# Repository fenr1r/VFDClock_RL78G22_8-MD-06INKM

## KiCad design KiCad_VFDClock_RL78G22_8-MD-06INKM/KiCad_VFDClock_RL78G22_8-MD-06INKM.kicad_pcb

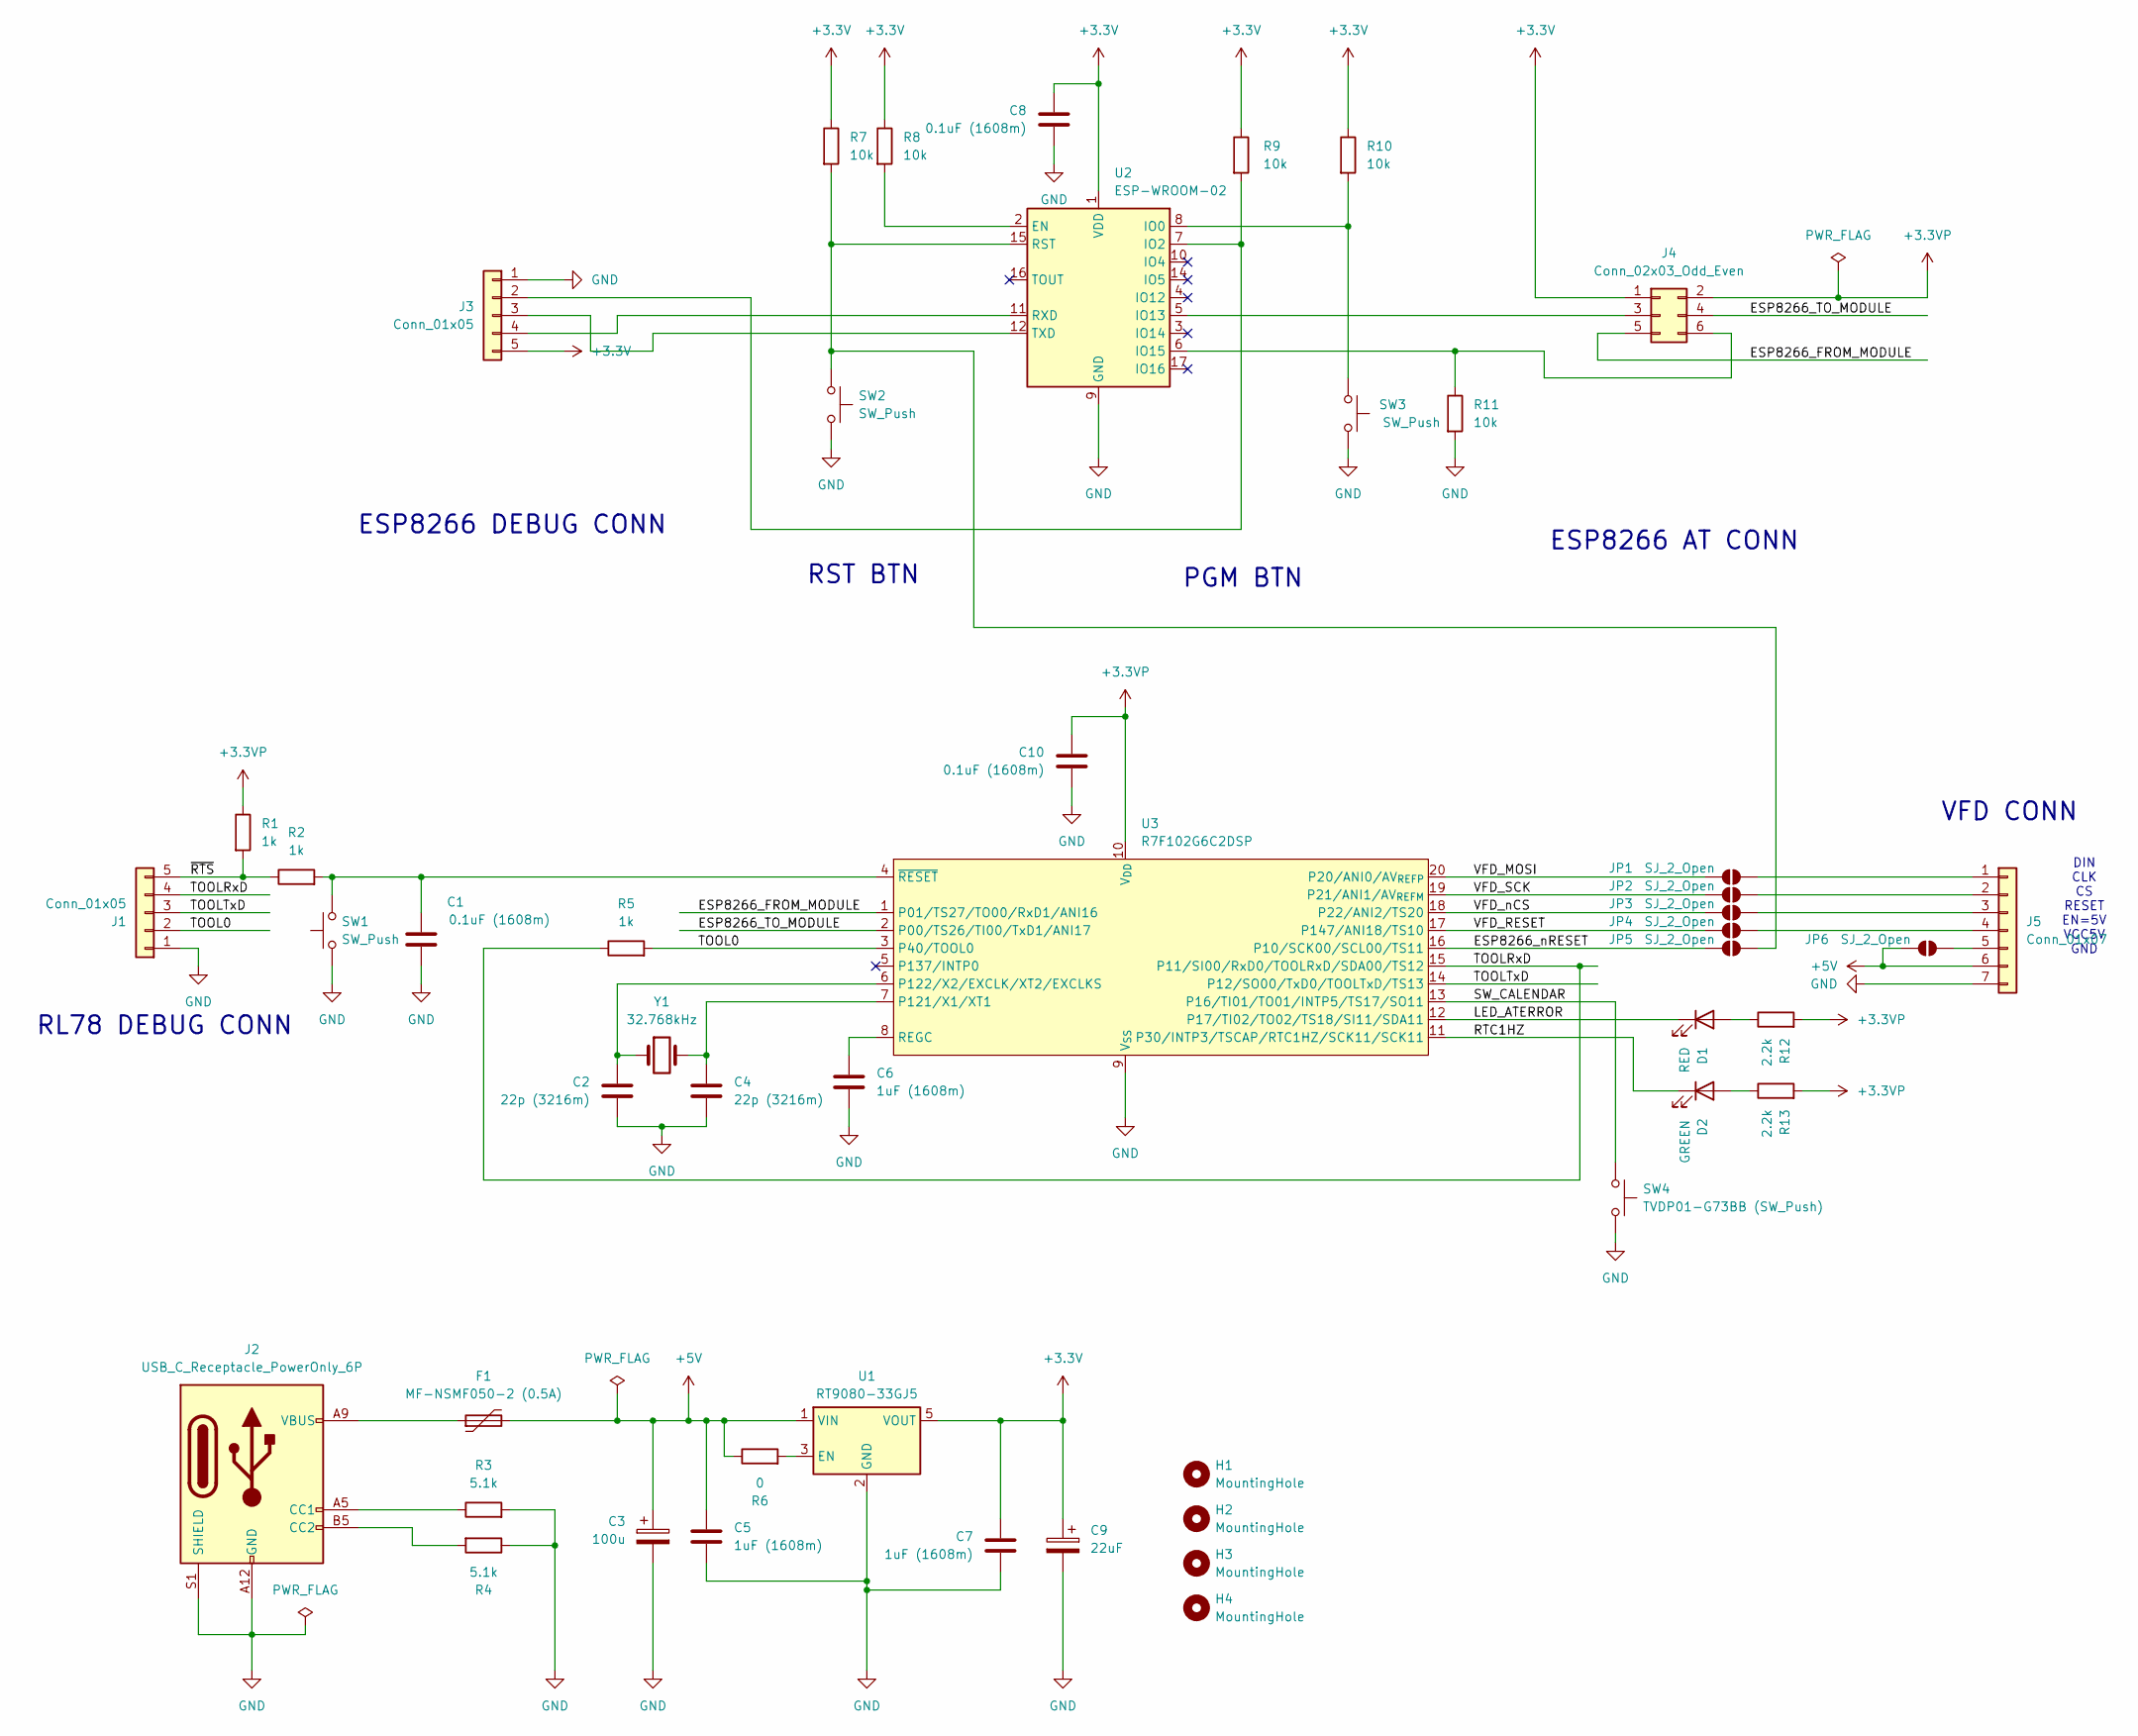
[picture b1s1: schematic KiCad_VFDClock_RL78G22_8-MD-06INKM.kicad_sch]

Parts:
C1, C8, C10: 0.1uF (1608m); C_0603_1608Metric_Pad1.08x0.95mm_HandSolder
C2, C4: 22p (3216m); C_1206_3216Metric_Pad1.33x1.80mm_HandSolder
C3: 100u; CP_Radial_D6.3mm_P2.50mm
C5, C6, C7: 1uF (1608m); C_0603_1608Metric_Pad1.08x0.95mm_HandSolder
C9: 22uF; CP_Radial_Tantal_D4.5mm_P2.50mm
D1: RED; LED_0603_1608Metric_Pad1.05x0.95mm_HandSolder
D2: GREEN; LED_0603_1608Metric_Pad1.05x0.95mm_HandSolder
F1: MF-NSMF050-2 (0.5A); C_1812_4532Metric_Pad1.57x3.40mm_HandSolder
H1, H2, H3, H4: MountingHole; MountingHole_2.2mm_M2
J1, J3: Conn_01x05; ConThrough_XB-3_1x05_P2.54mm_Vertical
J2: USB_C_Receptacle_PowerOnly_6P; USB_C_Receptacle_GCT_USB4125-xx-x_6P_TopMnt_Horizontal
J4: Conn_02x03_Odd_Even; PinHeader_2x03_P2.54mm_Vertical_SMD
J5: Conn_01x07; PinHeader_1x07_P2.54mm_Vertical
JP1, JP2, JP3, JP4, JP5, JP6: SJ_2_Open; SolderJumper-2_P1.3mm_Open_RoundedPad1.0x1.5mm
R1, R2, R5: 1k; R_0603_1608Metric_Pad0.98x0.95mm_HandSolder
R3, R4: 5.1k; R_0603_1608Metric_Pad0.98x0.95mm_HandSolder
R6: 0; R_0603_1608Metric_Pad0.98x0.95mm_HandSolder
R7, R8, R9, R10, R11: 10k; R_0603_1608Metric_Pad0.98x0.95mm_HandSolder
R12, R13: 2.2k; R_0603_1608Metric_Pad0.98x0.95mm_HandSolder
SW1, SW2, SW3: SW_Push; SW_PUSH_1P1T_6x3.5mm_H4.3_APEM_MJTP1243
SW4: TVDP01-G73BB (SW_Push); SW_PUSH_6mm
U1: RT9080-33GJ5; TSOT-23-5_HandSoldering
U2: ESP-WROOM-02
U3: R7F102G6C2DSP; TSSOP-20_4.4x6.5mm_P0.65mm
Y1: 32.768kHz; Crystal_DS26_D2.0mm_L6.0mm_Horizontal

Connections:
+3.3V: C7.1, C8.1, C9.1, J3.5, J4.1, R7.1, R8.1, R9.1, R10.1, U1.5 (VOUT), U2.1 (VDD)
+3.3VP: C10.1, J4.2, R1.1, R12.2, R13.2, U3.10 (V_{DD})
+5V: C3.1, C5.1, F1.2, J5.6, JP6.1 (A), R6.1, U1.1 (VIN)
/ESP8266_FROM_MODULE: J4.5, U3.1 (P01/TS27/TO00/RxD1/ANI16)
/ESP8266_TO_MODULE: J4.4, U3.2 (P00/TS26/TI00/TxD1/ANI17)
/ESP8266_nRESET: JP5.1 (A), U3.16 (P10/SCK00/SCL00/TS11)
/LED_ATERROR: D1.1 (K), U3.12 (P17/TI02/TO02/TS18/SI11/SDA11)
/RTC1HZ: D2.1 (K), U3.11 (P30/INTP3/TSCAP/RTC1HZ/SCK11/SCK11)
/SW_CALENDAR: SW4.1, U3.13 (P16/TI01/TO01/INTP5/TS17/SO11)
/TOOL0: J1.2, R5.2, U3.3 (P40/TOOL0)
/TOOLRxD: J1.4, R5.1, U3.15 (P11/SI00/RxD0/TOOLRxD/SDA00/TS12)
/TOOLTxD: J1.3, U3.14 (P12/SO00/TxD0/TOOLTxD/TS13)
/VFD_MOSI: JP1.1 (A), U3.20 (P20/ANI0/AV_{REFP})
/VFD_RESET: JP4.1 (A), U3.17 (P147/ANI18/TS10)
/VFD_SCK: JP2.1 (A), U3.19 (P21/ANI1/AV_{REFM})
/VFD_nCS: JP3.1 (A), U3.18 (P22/ANI2/TS20)
/~RTS: J1.5, R1.2, R2.1
GND: C1.2, C2.2, C3.2, C4.2, C5.2, C6.2, C7.2, C8.2, C9.2, C10.2, J1.1, J2.A12 (GND), J2.B12 (GND), J2.S1 (SHIELD), J3.1, J5.7, R3.2, R4.1, R11.2, SW1.1, SW2.2, SW3.2, SW4.2, U1.2 (GND), U2.9 (GND), U2.13 (GND), U2.18 (GND), U2.19 (GND), U3.9 (V_{SS})
unnamed: D1.2 (A), R12.1
unnamed: D2.2 (A), R13.1
unnamed: F1.1, J2.A9 (VBUS), J2.B9 (VBUS)
unnamed: J2.A5 (CC1), R3.1
unnamed: J2.B5 (CC2), R4.2
unnamed: J3.2, R9.2, U2.7 (IO2)
unnamed: J3.3, U2.12 (TXD)
unnamed: J3.4, U2.11 (RXD)
unnamed: J4.3, U2.5 (IO13)
unnamed: J4.6, R11.1, U2.6 (IO15)
unnamed: J5.1, JP1.2 (B)
unnamed: J5.2, JP2.2 (B)
unnamed: J5.3, JP3.2 (B)
unnamed: J5.4, JP4.2 (B)
unnamed: J5.5, JP6.2 (B)
unnamed: JP5.2 (B), R7.2, SW2.1, U2.15 (RST)
unnamed: R6.2, U1.3 (EN)
unnamed: R8.2, U2.2 (EN)
unnamed: R10.2, SW3.1, U2.8 (IO0)
unnamed: C4.1, U3.7 (P121/X1/XT1), Y1.2
unnamed: C2.1, U3.6 (P122/X2/EXCLK/XT2/EXCLKS), Y1.1
unnamed: C6.1, U3.8 (REGC)
unnamed: C1.1, R2.2, SW1.2, U3.4 (~RESET)

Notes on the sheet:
RST BTN
PGM BTN
VFD CONN
RL78 DEBUG CONN
ESP8266 AT CONN
ESP8266 DEBUG CONN
DIN CLK CS RESET EN=5V VCC5V GND

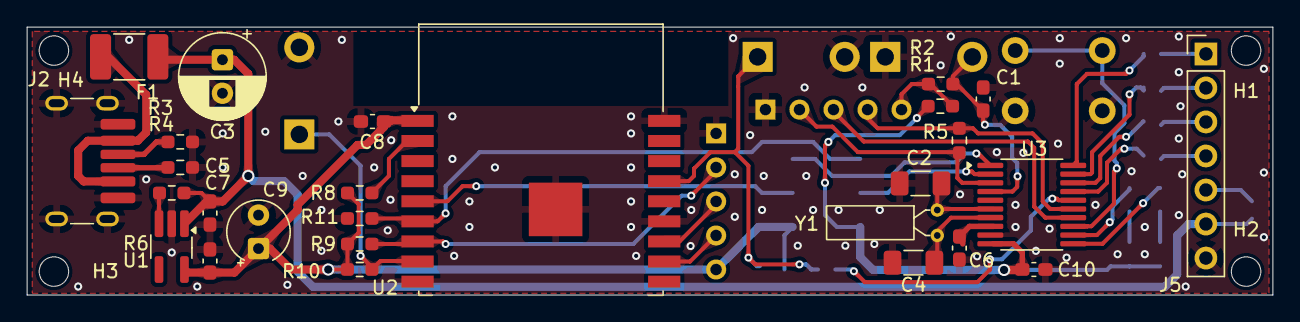
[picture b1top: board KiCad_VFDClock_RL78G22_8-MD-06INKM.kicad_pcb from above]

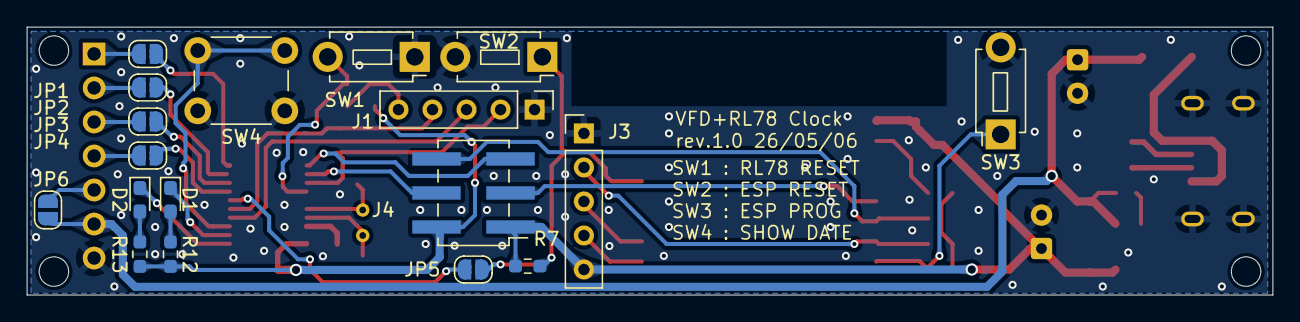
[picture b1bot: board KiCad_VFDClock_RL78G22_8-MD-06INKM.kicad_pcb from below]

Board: 2 copper layers, 93.0 x 20.0 mm, 49 parts (18 on the bottom side), 41 nets.

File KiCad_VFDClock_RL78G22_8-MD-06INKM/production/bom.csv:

Designator,Footprint,Quantity,Value,LCSC Part #
"C1, C10, C8",0603,3,0.1uF (1608m),
"C2, C4",1206,2,22p (3216m),
C3,CP_Radial_D6.3mm_P2.50mm,1,100u,
"C5, C6, C7",0603,3,1uF (1608m),
C9,CP_Radial_Tantal_D4.5mm_P2.50mm,1,22uF,
D1,0603,1,RED,
D2,0603,1,GREEN,
F1,1812,1,MF-NSMF050-2 (0.5A),
"J1, J3",ConThrough_XB-3_1x05_P2.54mm_Vertical,2,Conn_01x05,
J2,USB_C_Receptacle_GCT_USB4125-xx-x_6P_TopMnt_Horizontal,1,USB_C_Receptacle_PowerOnly_6P,
J4,PinHeader_2x03_P2.54mm_Vertical_SMD,1,Conn_02x03_Odd_Even,
J5,PinHeader_1x07_P2.54mm_Vertical,1,Conn_01x07,
"R1, R2, R5",0603,3,1k,
"R10, R11, R7, R8, R9",0603,5,10k,
"R12, R13",0603,2,2.2k,
"R3, R4",0603,2,5.1k,
R6,0603,1,0,
"SW1, SW2, SW3",SW_PUSH_1P1T_6x3.5mm_H4.3_APEM_MJTP1243,3,SW_Push,
SW4,SW_PUSH_6mm,1,TVDP01-G73BB (SW_Push),
U1,TSOT-23-5_HandSoldering,1,RT9080-33GJ5,
U2,ESP-WROOM-02,1,ESP-WROOM-02,
U3,TSSOP-20_4.4x6.5mm_P0.65mm,1,R7F102G6C2DSP,
Y1,Crystal_DS26_D2.0mm_L6.0mm_Horizontal,1,32.768kHz,

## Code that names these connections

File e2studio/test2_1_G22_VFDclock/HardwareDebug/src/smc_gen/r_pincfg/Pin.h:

/*
* Copyright (c) 2021 - 2025 Renesas Electronics Corporation and/or its affiliates
*
* SPDX-License-Identifier: BSD-3-Clause
*/

/***********************************************************************************************************************
* File Name        : Pin.h
* Version          : 1.0.0
* Device(s)        : R7F102G6CxSP
* Description      : This file implements SMC pin code generation.
***********************************************************************************************************************/


#ifndef PIN_H
#define PIN_H

/***********************************************************************************************************************
Macro definitions (Register bit)
***********************************************************************************************************************/

/***********************************************************************************************************************
Macro definitions
***********************************************************************************************************************/

/* User's guide for symbolic name.
 * The generated symbolic names can be used in the user application as follows: 
 *
 * Example: Toggle LED1 at Pin P54.
 *  There are 2 ways to toggle LED1
 *   1) Using symbolic name macro
 *    Assuming the symbolic name for P54 is "LED1", the generated macro definition will be:
 *         #define LED1    5,4
 *
 *    To use this macro definition to toggle the LED1, call the symbolic name APIs:
 *         PIN_WRITE(LED1) = ~PIN_READ(LED1)
 *
 *   2) Not using symbolic name macro
 *    Call the symbolic name APIs directly
 *         PIN_WRITE(5,4) = ~PIN_READ(5,4)
 */

/* Symbolic name */
#define LED_ATERROR        1,7
#define SW_CALENDAR        1,6
#define ESP8266_nRESET        1,0
#define VFD_RESET        14,7
#define VFD_nCS        2,2
#define VFD_SCK        2,1
#define VFD_MOSI        2,0

/* Pin write helper */
#define PIN_WRITE_HELPER(x,y)                    ((P##x##_bit.no##y))
/* Pin read helper */
#define PIN_READ_HELPER(x,y)                     ((P##x##_bit.no##y))

/* Pin write API */
#define PIN_WRITE(...)                           (PIN_WRITE_HELPER(__VA_ARGS__))
/* Pin read API */
#define PIN_READ(...)                            (PIN_READ_HELPER(__VA_ARGS__))

/***********************************************************************************************************************
Typedef definitions
***********************************************************************************************************************/

/***********************************************************************************************************************
Global functions
***********************************************************************************************************************/
void R_Pins_Create(void);
/* Start user code for function. Do not edit comment generated here */
/* End user code. Do not edit comment generated here */
#endif
